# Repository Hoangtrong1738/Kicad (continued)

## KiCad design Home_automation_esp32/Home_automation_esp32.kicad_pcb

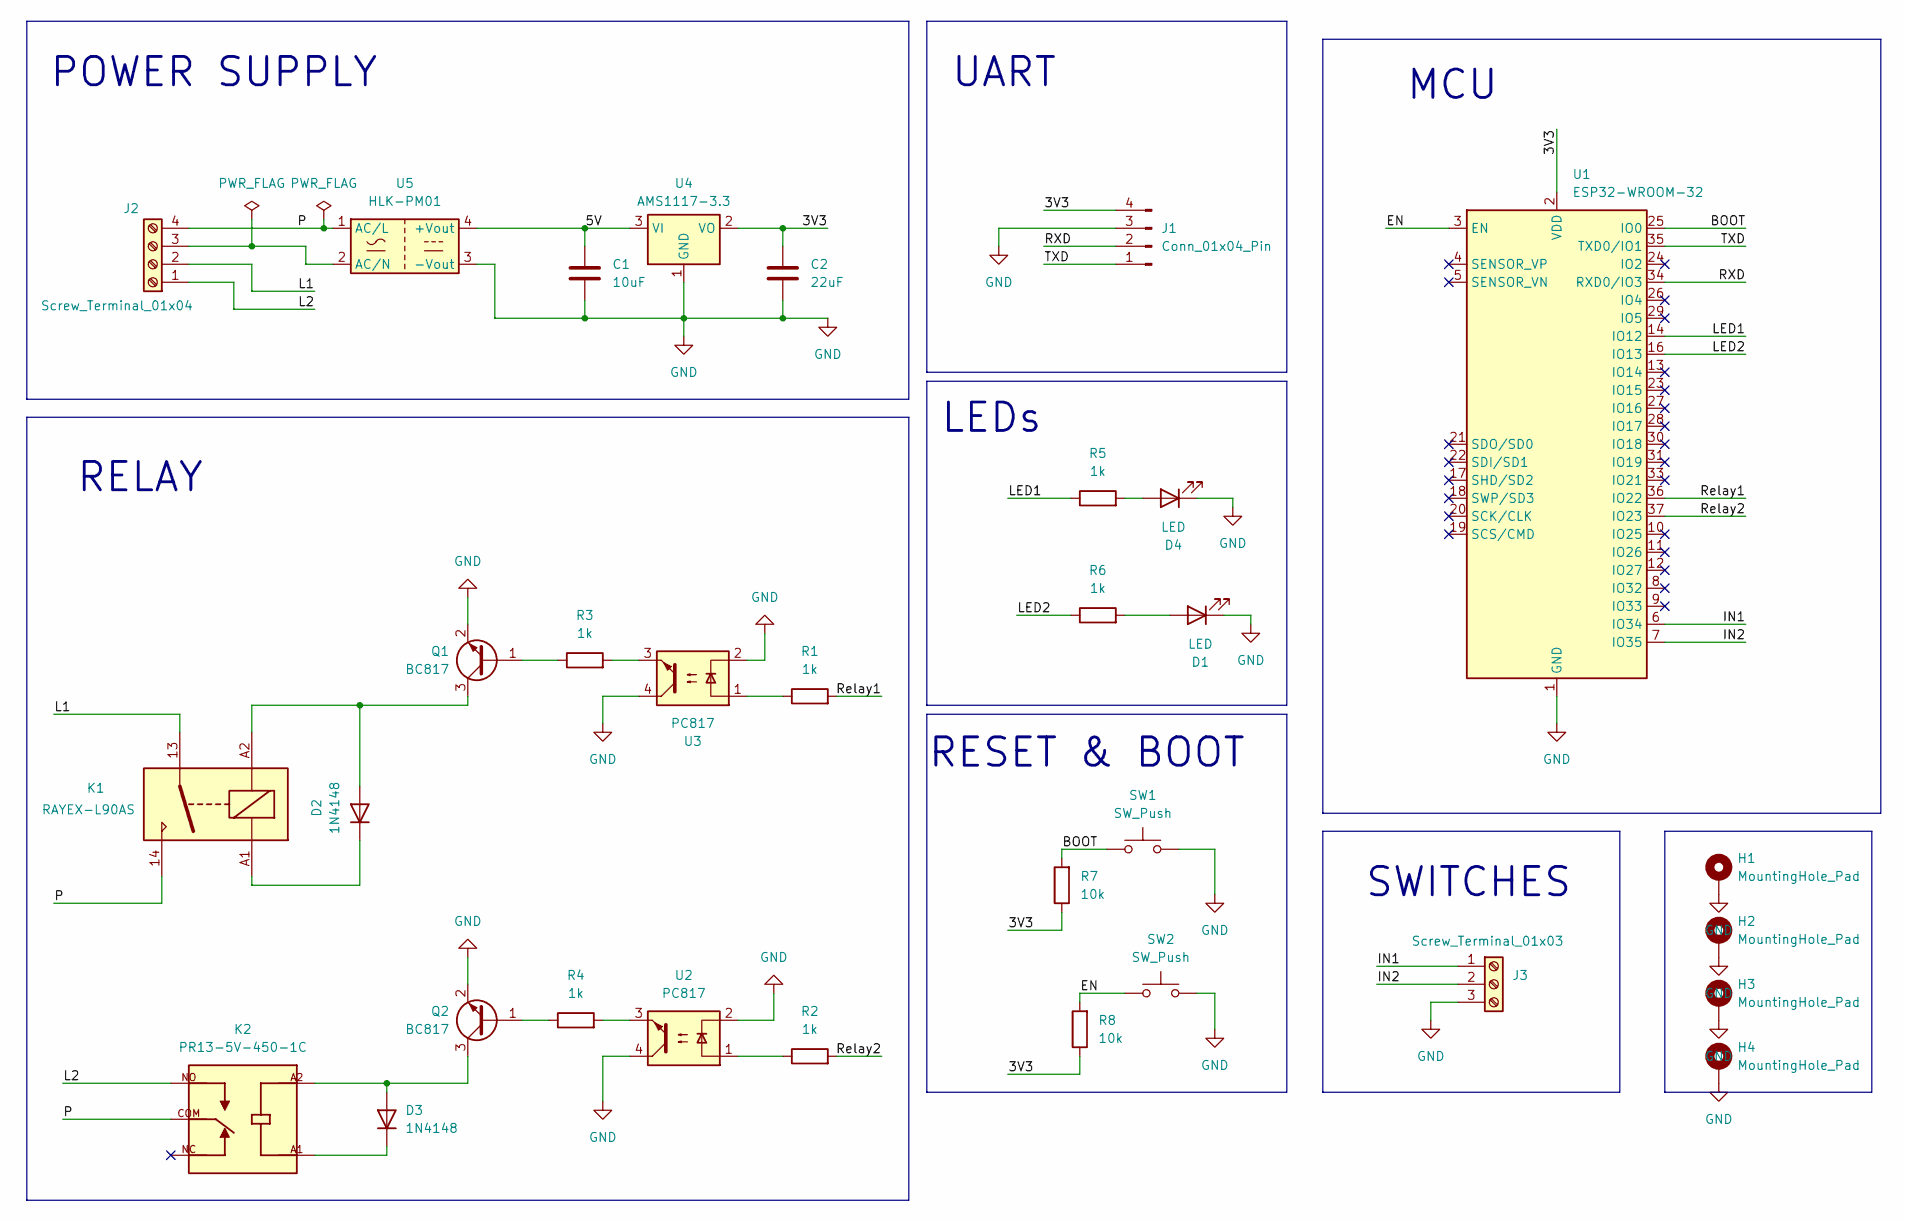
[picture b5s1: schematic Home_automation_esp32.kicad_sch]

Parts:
C1: 10uF; C_0805_2012Metric
C2: 22uF; C_0805_2012Metric
D1, D4: LED; LED_0805_2012Metric
D2, D3: 1N4148; D_DO-35_SOD27_P7.62mm_Horizontal
H1, H2, H3, H4: MountingHole_Pad; MountingHole_2.2mm_M2_DIN965_Pad
J1: Conn_01x04_Pin; PinHeader_1x04_P2.54mm_Vertical
J2: Screw_Terminal_01x04; TerminalBlock_MaiXu_MX126-5.0-04P_1x04_P5.00mm
J3: Screw_Terminal_01x03; TerminalBlock_MaiXu_MX126-5.0-03P_1x03_P5.00mm
K1: RAYEX-L90AS; Relay_SPST_RAYEX-L90AS
K2: PR13-5V-450-1C; RELAY_PR13-5V-450-1C; PARTREV 1.0
Q1, Q2: BC817; SOT-23
R1, R2, R3, R4, R5, R6: 1k; R_0805_2012Metric
R7, R8: 10k; R_0805_2012Metric
SW1, SW2: SW_Push; SW_PUSH_6mm
U1: ESP32-WROOM-32
U2, U3: PC817; DIP-4_W7.62mm
U4: AMS1117-3.3; SOT-223-3_TabPin2
U5: HLK-PM01; Converter_ACDC_Hi-Link_HLK-PMxx

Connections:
/3V3: C2.1, J1.4, R7.1, R8.1, U1.2 (VDD), U4.2 (VO)
/5V: C1.1, U4.3 (VI), U5.4 (+Vout)
/<NO NET>: R1.2, U1.36 (IO22)
/BOOT: R7.2, SW1.1, U1.25 (IO0)
/EN: R8.2, SW2.1, U1.3 (EN)
/IN1: J3.1, U1.6 (IO34)
/IN2: J3.2, U1.7 (IO35)
/L1: J2.2, K1.13
/L2: J2.1, K2.NO
/LED1: R5.1, U1.14 (IO12)
/LED2: R6.1, U1.16 (IO13)
/P: J2.4, K1.14, K2.COM, U5.1 (AC/L)
/RXD: J1.2, U1.34 (RXD0/IO3)
/Relay2: R2.2, U1.37 (IO23)
/TXD: J1.1, U1.35 (TXD0/IO1)
GND: C1.2, C2.2, D1.1 (K), D4.1 (K), H1.1 (1_1), H2.1 (1_1), H3.1 (1_1), H4.1 (1_1), J1.3, J3.3, Q1.2 (E), Q2.2 (E), SW1.2, SW2.2, U1.1 (GND), U1.15 (GND), U1.38 (GND), U1.39 (GND), U2.2, U2.4, U3.2, U3.4, U4.1 (GND), U5.3 (-Vout)
unnamed: D1.2 (A), R6.2
unnamed: D2.2 (A), K1.A2, Q1.3 (C)
unnamed: D2.1 (K), K1.A1
unnamed: D3.2 (A), K2.A2, Q2.3 (C)
unnamed: D3.1 (K), K2.A1
unnamed: D4.2 (A), R5.2
unnamed: J2.3, U5.2 (AC/N)
unnamed: Q1.1 (B), R3.1
unnamed: Q2.1 (B), R4.1
unnamed: R1.1, U3.1
unnamed: R2.1, U2.1
unnamed: R3.2, U3.3
unnamed: R4.2, U2.3

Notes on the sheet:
RESET & BOOT
MCU
UART
LEDs
RELAY
SWITCHES
POWER SUPPLY

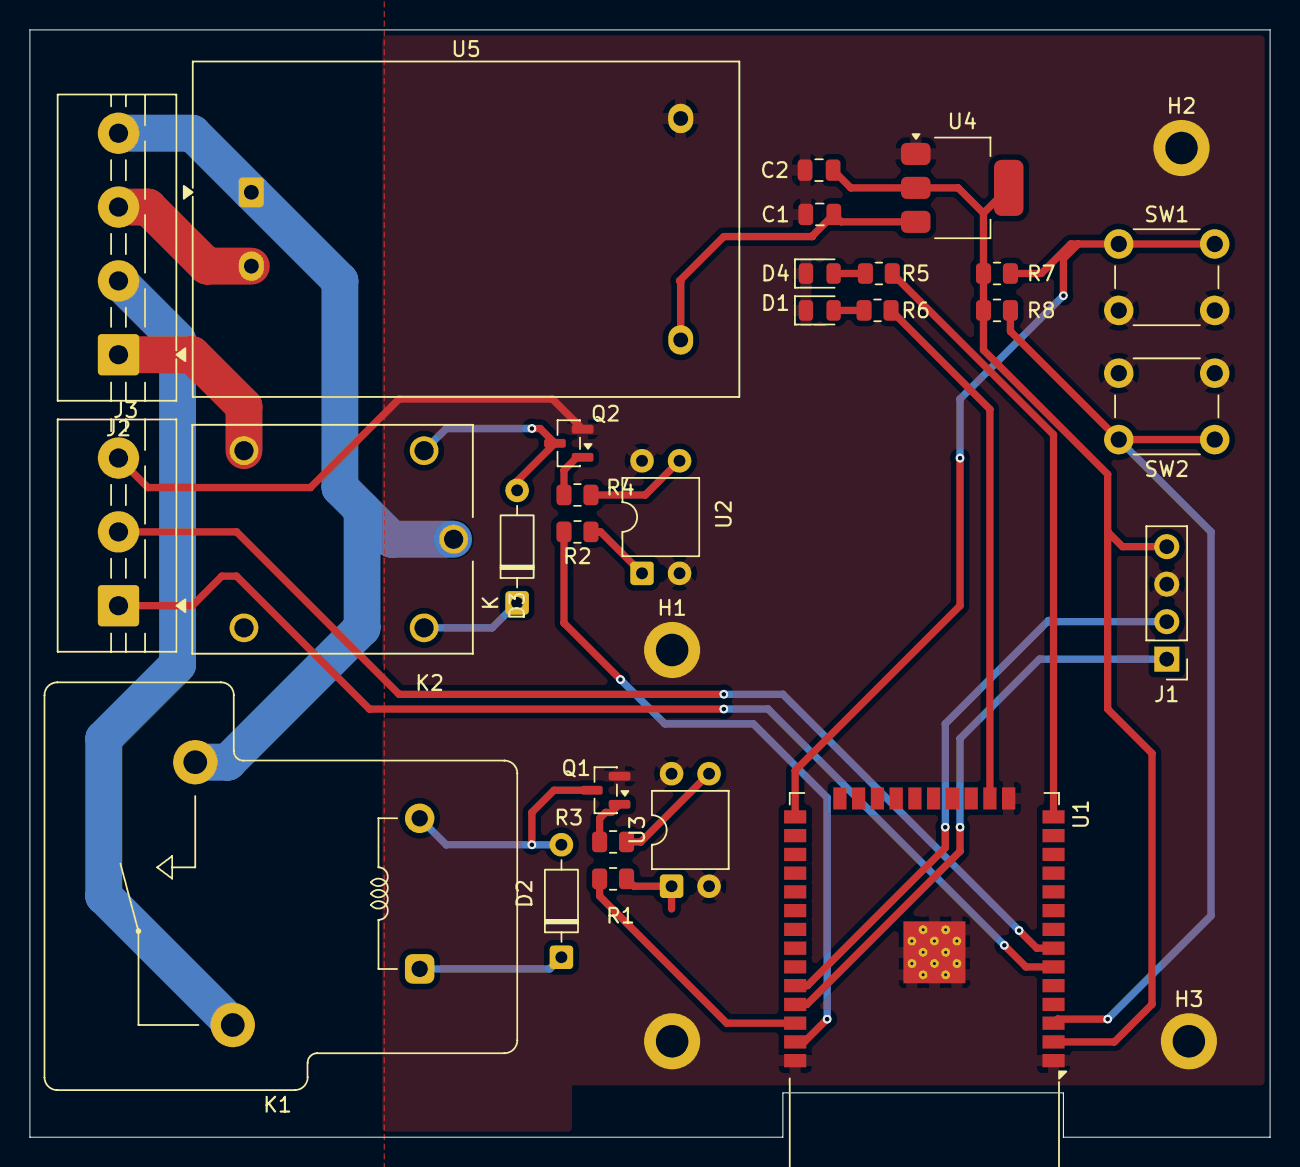
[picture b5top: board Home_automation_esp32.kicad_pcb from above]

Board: 2 copper layers, 84.0 x 75.0 mm, 32 parts (0 on the bottom side), 29 nets.

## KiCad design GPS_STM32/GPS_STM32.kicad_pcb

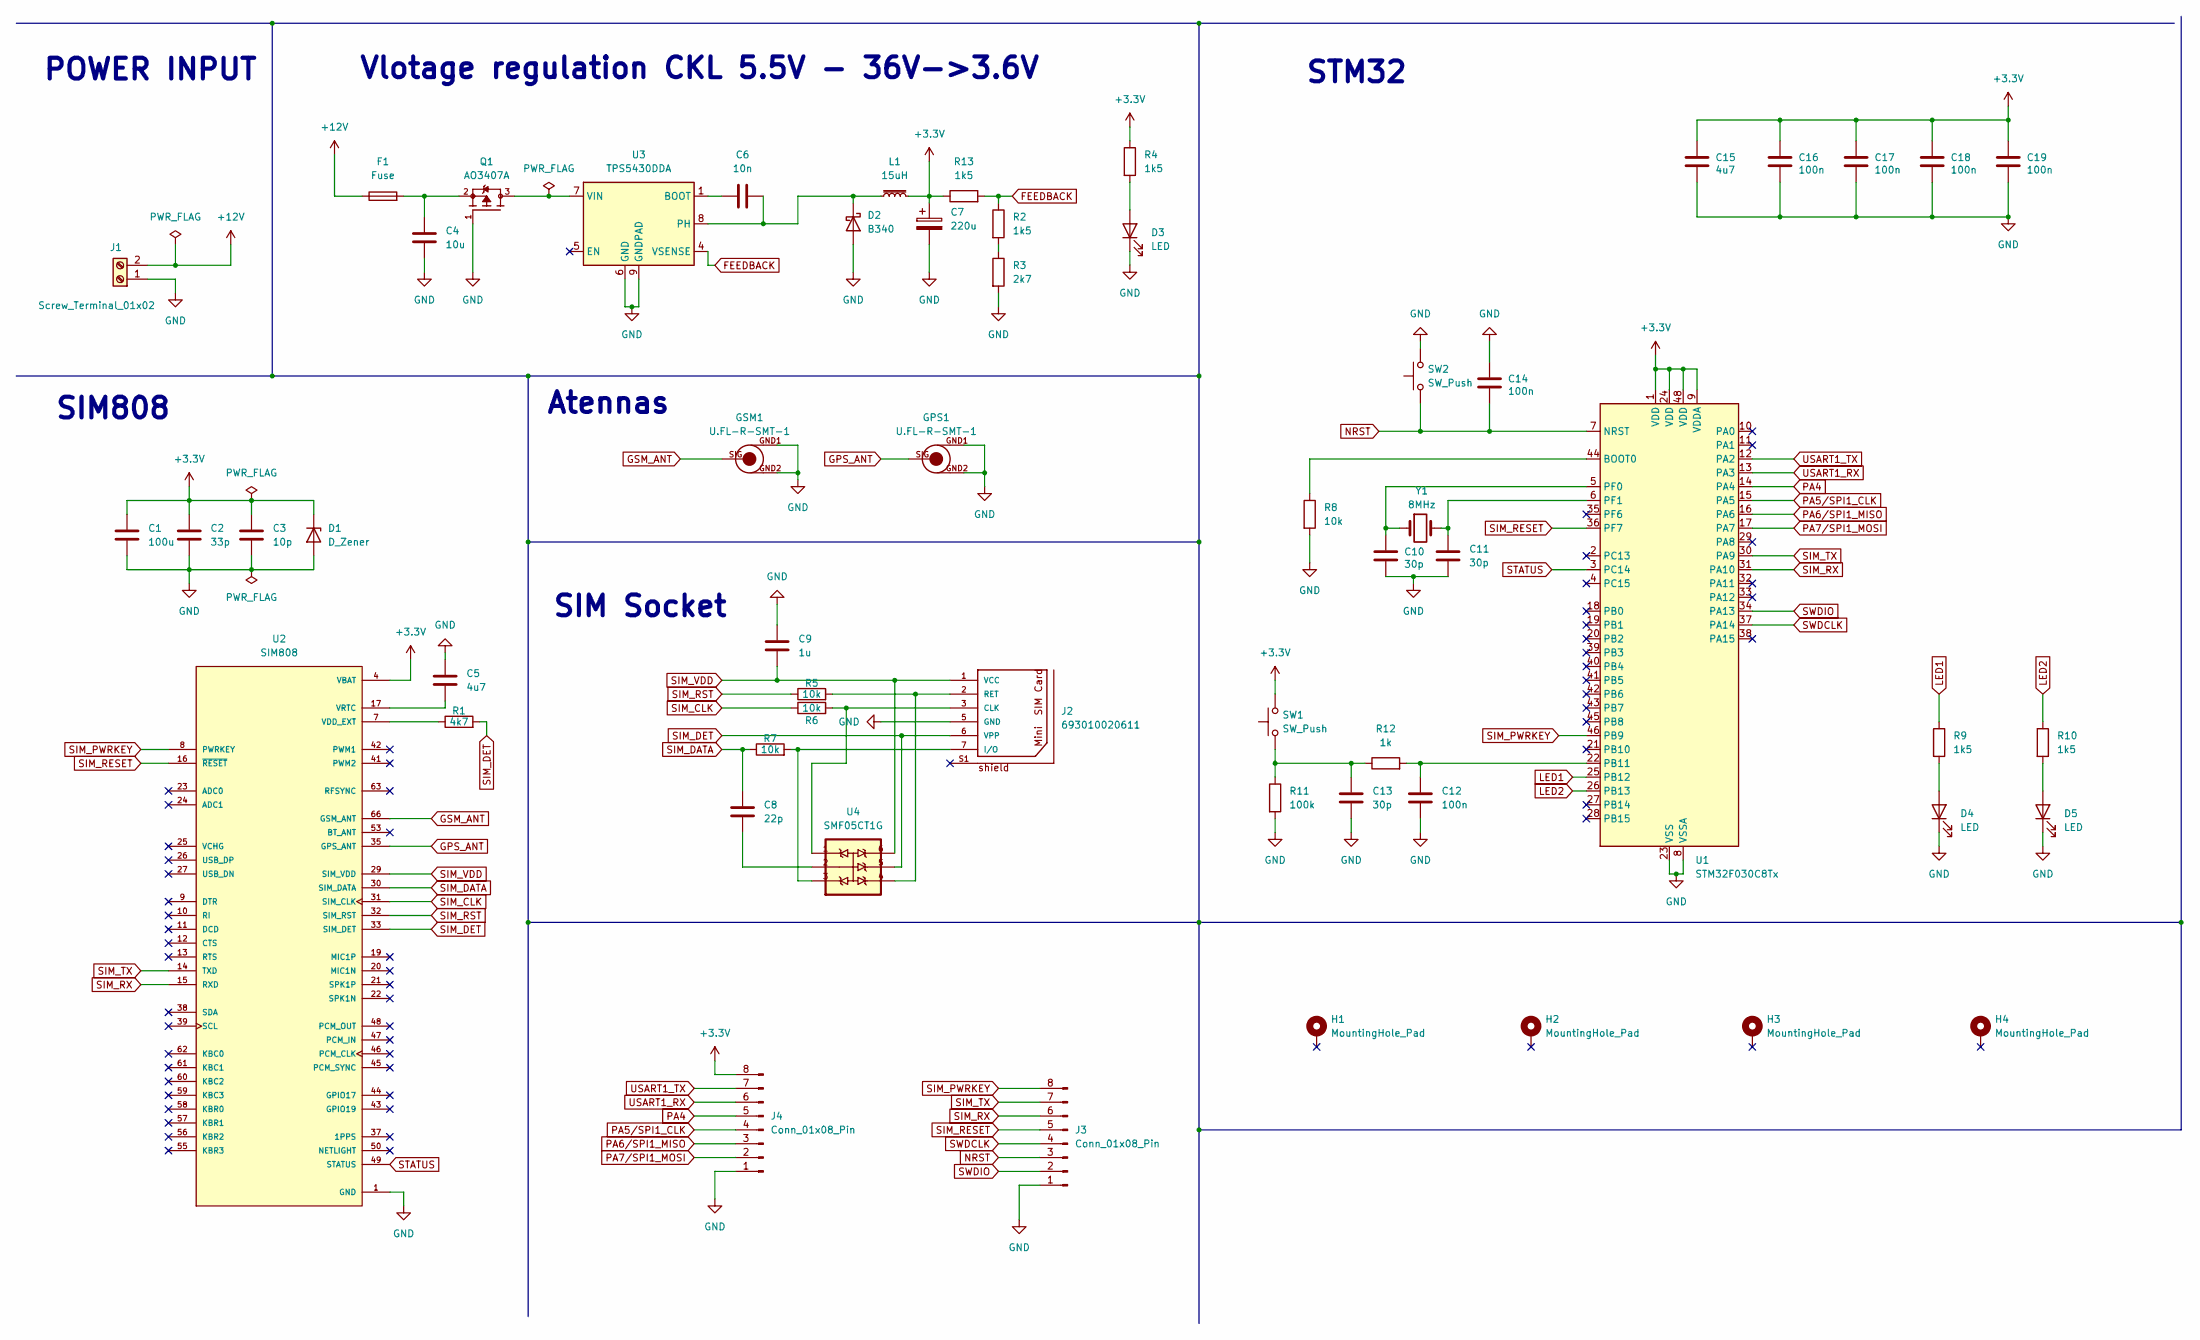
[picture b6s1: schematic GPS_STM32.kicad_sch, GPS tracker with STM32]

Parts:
C1: 100u; C_1206_3216Metric
C2: 33p; C_0402_1005Metric
C3: 10p; C_0402_1005Metric
C4: 10u; C_0805_2012Metric
C5, C15: 4u7; C_0201_0603Metric
C6: 10n; C_0201_0603Metric
C7: 220u; CP_EIA-7343-15_Kemet-W
C8: 22p; C_0402_1005Metric
C9: 1u; C_0402_1005Metric
C10, C11, C13: 30p; C_0402_1005Metric
C12, C14, C19: 100n; C_0402_1005Metric
C16, C17, C18: 100n; C_0402_1005Metric_Pad0.74x0.62mm_HandSolder
D1: D_Zener; D_0805_2012Metric
D2: B340; D_SMC
D3, D4, D5: LED; LED_0201_0603Metric
F1: Fuse; LED_0201_0603Metric
GPS1: U.FL-R-SMT-1
GSM1: U.FL-R-SMT-1
H1, H2, H3, H4: MountingHole_Pad; MountingHole_2.2mm_M2_Pad_Via
J1: Screw_Terminal_01x02; TerminalBlock_Phoenix_MKDS-1,5-2-5.08_1x02_P5.08mm_Horizont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
J2: 693010020611
J3, J4: Conn_01x08_Pin; PinHeader_1x08_P2.54mm_Vertical
L1: 15uH; L_10.4x10.4_H4.8
Q1: AO3407A; SOT95P280X125-3N; PARTREV 5
R1: 4k7; R_0402_1005Metric
R2, R4, R9, R10, R13: 1k5; R_0805_2012Metric
R3: 2k7; R_0805_2012Metric
R5, R6, R7, R8: 10k; R_0402_1005Metric
R11: 100k; R_0201_0603Metric
R12: 1k; R_0603_1608Metric
SW1, SW2: SW_Push; SW_Push_1P1T_NO_CK_KSC6xxJ
U1: STM32F030C8Tx; LQFP-48_7x7mm_P0.5mm
U2: SIM808; XCVR_SIM808; PARTREV 1.03
U3: TPS5430DDA; TI_SO-PowerPAD-8_ThermalVias
U4: SMF05CT1G; SOT65P210X110-6N
Y1: 8MHz; Crystal_SMD_5032-2Pin_5.0x3.2mm

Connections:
+3.3V: C1.1, C2.1, C3.1, C7.1, C15.1, C16.1, C17.1, C18.1, C19.1, D1.1 (K), J4.8, L1.2, R4.1, R13.1, SW1.2, U1.1 (VDD), U1.9 (VDDA), U1.24 (VDD), U1.48 (VDD), U2.4 (VBAT), U2.5 (VBAT), U2.6 (VBAT)
+12V: F1.1, J1.2
FEEDBACK: R2.1, R13.2, U3.4 (VSENSE)
GND: C1.2, C2.2, C3.2, C4.2, C5.1, C7.2, C9.1, C10.2, C11.2, C12.2, C13.2, C14.1, C15.2, C16.2, C17.2, C18.2, C19.2, D1.2 (A), D2.2 (A), D3.1 (K), D4.1 (K), D5.1 (K), GPS1.GND1, GPS1.GND2, GSM1.GND1, GSM1.GND2, J1.1, J2.5 (GND), J3.1, J4.1, Q1.1, R3.2, R8.2, R11.2, SW2.2, U1.8 (VSSA), U1.23 (VSS), U1.47 (VSS), U2.1 (GND), U2.2 (GND), U2.3 (GND), U2.18 (GND), U2.28 (GND), U2.34 (GND), U2.36 (GND), U2.40 (GND), U2.51 (GND), U2.52 (GND), U2.54 (GND), U2.64 (GND), U2.65 (GND), U2.67 (GND), U2.68 (GND), U3.6 (GND), U3.9 (GNDPAD)
GPS_ANT: GPS1.SIG, U2.35 (GPS_ANT)
GSM_ANT: GSM1.SIG, U2.66 (GSM_ANT)
LED1: R9.1, U1.25 (PB12)
LED2: R10.1, U1.26 (PB13)
NRST: C14.2, J3.3, SW2.1, U1.7 (NRST)
unnamed: C4.1, F1.2, Q1.2
unnamed: C8.2, U4.2
unnamed: C13.1, R11.1, R12.1, SW1.1
unnamed: C6.2, D2.1 (K), L1.1, U3.8 (PH)
unnamed: D3.2 (A), R4.2
unnamed: D4.2 (A), R9.2
unnamed: D5.2 (A), R10.2
unnamed: J2.3 (CLK), R6.2, U4.1
unnamed: J2.7 (I/O), R7.2, U4.3
unnamed: J2.2 (RET), R5.2, U4.4
unnamed: R2.2, R3.1
unnamed: R8.1, U1.44 (BOOT0)
unnamed: C12.1, R12.2, U1.22 (PB11)
unnamed: C10.1, U1.5 (PF0), Y1.1
unnamed: C11.1, U1.6 (PF1), Y1.2
unnamed: R1.1, U2.7 (VDD_EXT)
unnamed: C5.2, U2.17 (VRTC)
unnamed: C6.1, U3.1 (BOOT)
unnamed: Q1.3, U3.7 (VIN)
PA4: J4.5, U1.14 (PA4)
PA5/SPI1_CLK: J4.4, U1.15 (PA5)
PA6/SPI1_MISO: J4.3, U1.16 (PA6)
PA7/SPI1_MOSI: J4.2, U1.17 (PA7)
SIM_CLK: R6.1, U2.31 (SIM_CLK)
SIM_DATA: C8.1, R7.1, U2.30 (SIM_DATA)
SIM_DET: J2.6 (VPP), R1.2, U2.33 (SIM_DET), U4.5
SIM_PWRKEY: J3.8, U1.46 (PB9), U2.8 (PWRKEY)
SIM_RESET: J3.5, U1.36 (PF7), U2.16 (~RESET)
SIM_RST: R5.1, U2.32 (SIM_RST)
SIM_RX: J3.6, U1.31 (PA10), U2.15 (RXD)
SIM_TX: J3.7, U1.30 (PA9), U2.14 (TXD)
SIM_VDD: C9.2, J2.1 (VCC), U2.29 (SIM_VDD), U4.6
STATUS: U1.3 (PC14), U2.49 (STATUS)
SWDCLK: J3.4, U1.37 (PA14)
SWDIO: J3.2, U1.34 (PA13)
USART1_RX: J4.6, U1.13 (PA3)
USART1_TX: J4.7, U1.12 (PA2)

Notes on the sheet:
SIM808
Vlotage regulation CKL 5.5V - 36V->3.6V
STM32
POWER INPUT
SIM Socket
Atennas

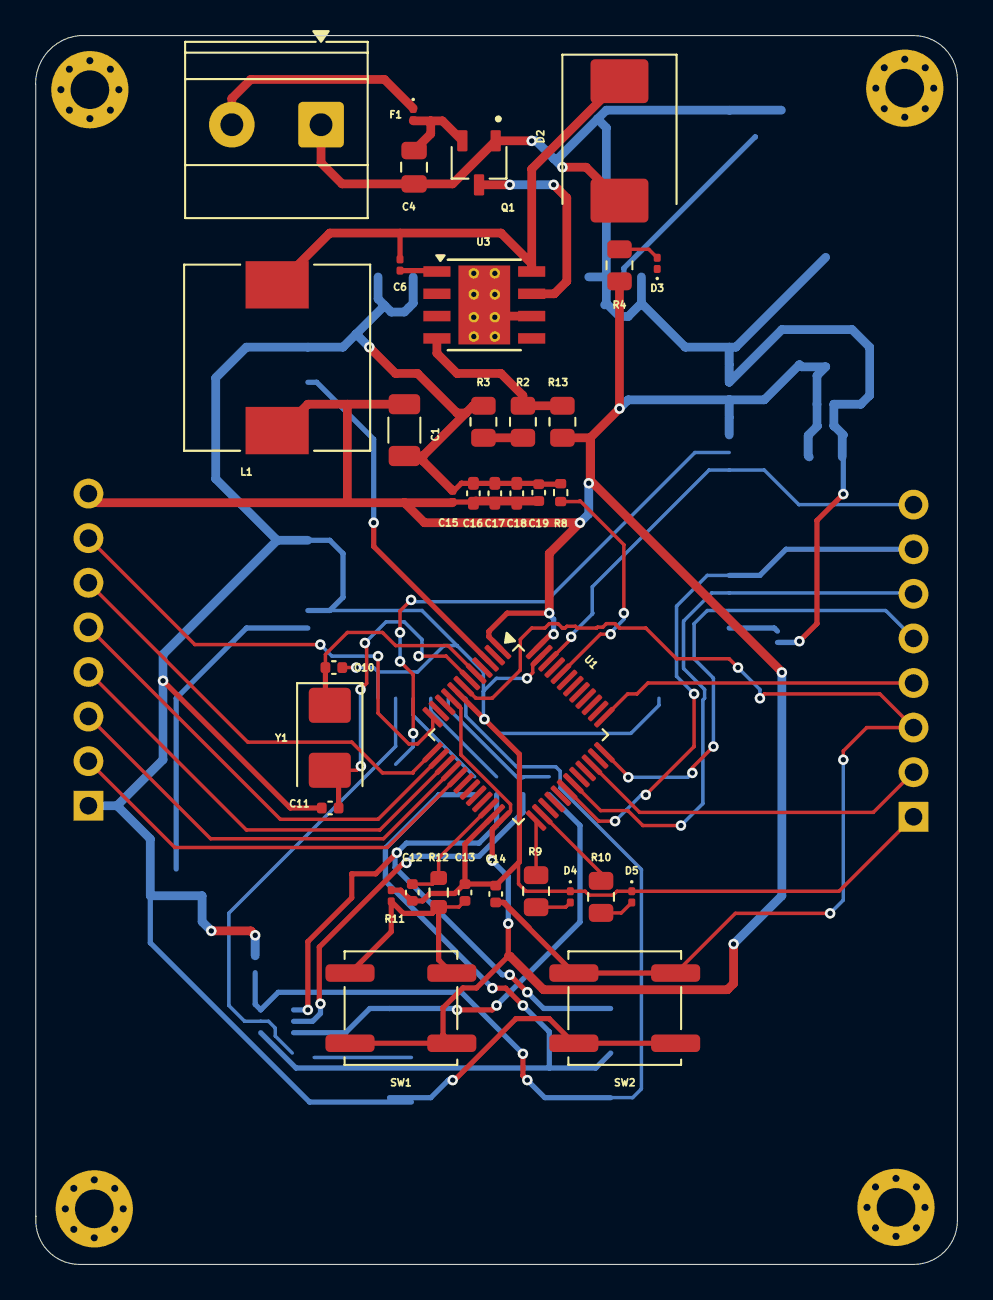
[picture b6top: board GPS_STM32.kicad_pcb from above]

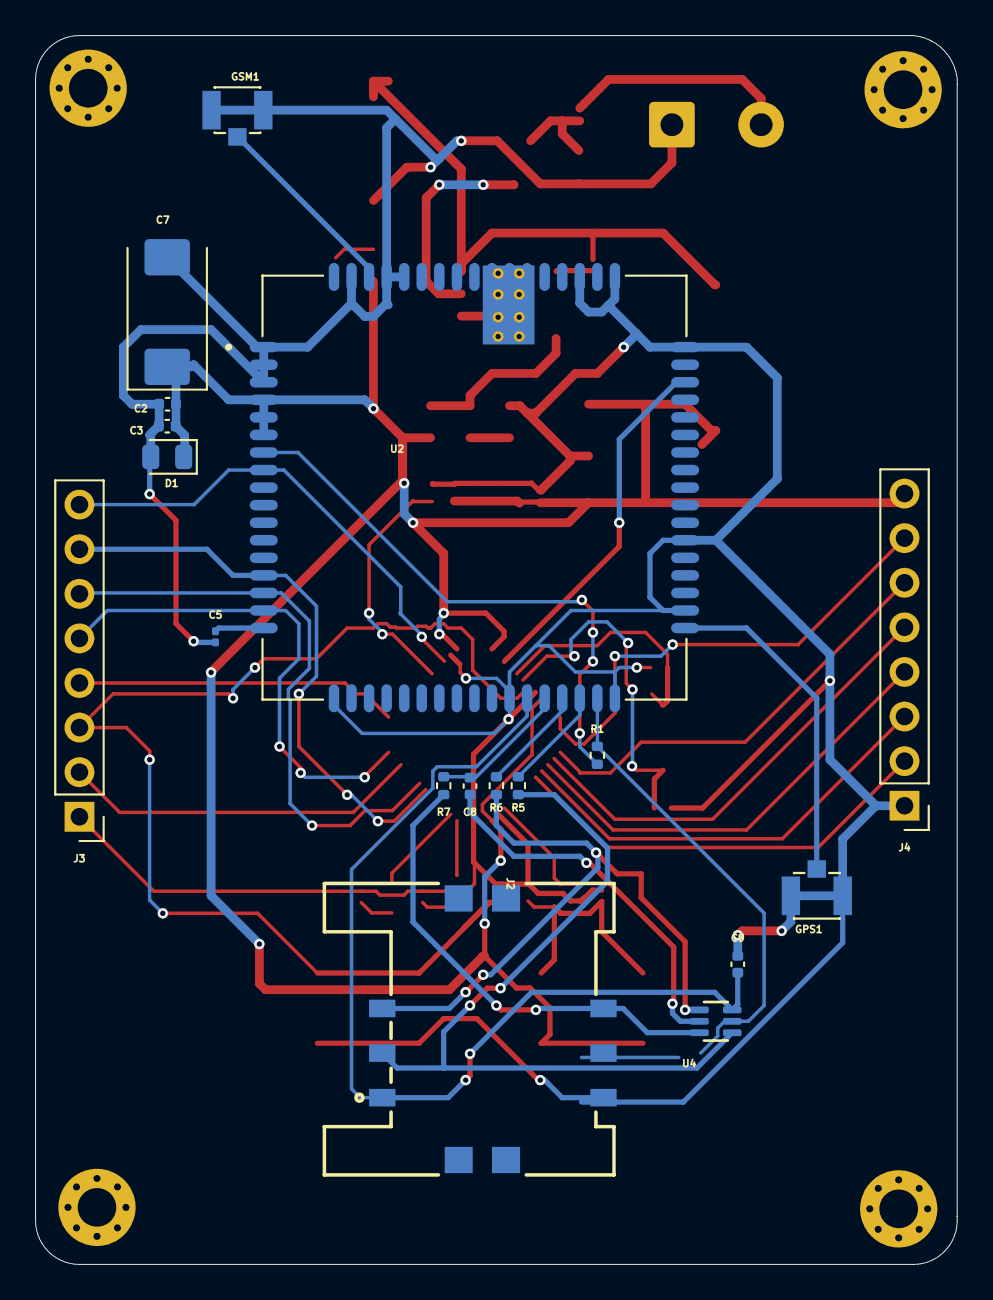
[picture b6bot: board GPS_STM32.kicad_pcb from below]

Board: 4 copper layers, 52.5 x 70.0 mm, 57 parts (18 on the bottom side), 46 nets.

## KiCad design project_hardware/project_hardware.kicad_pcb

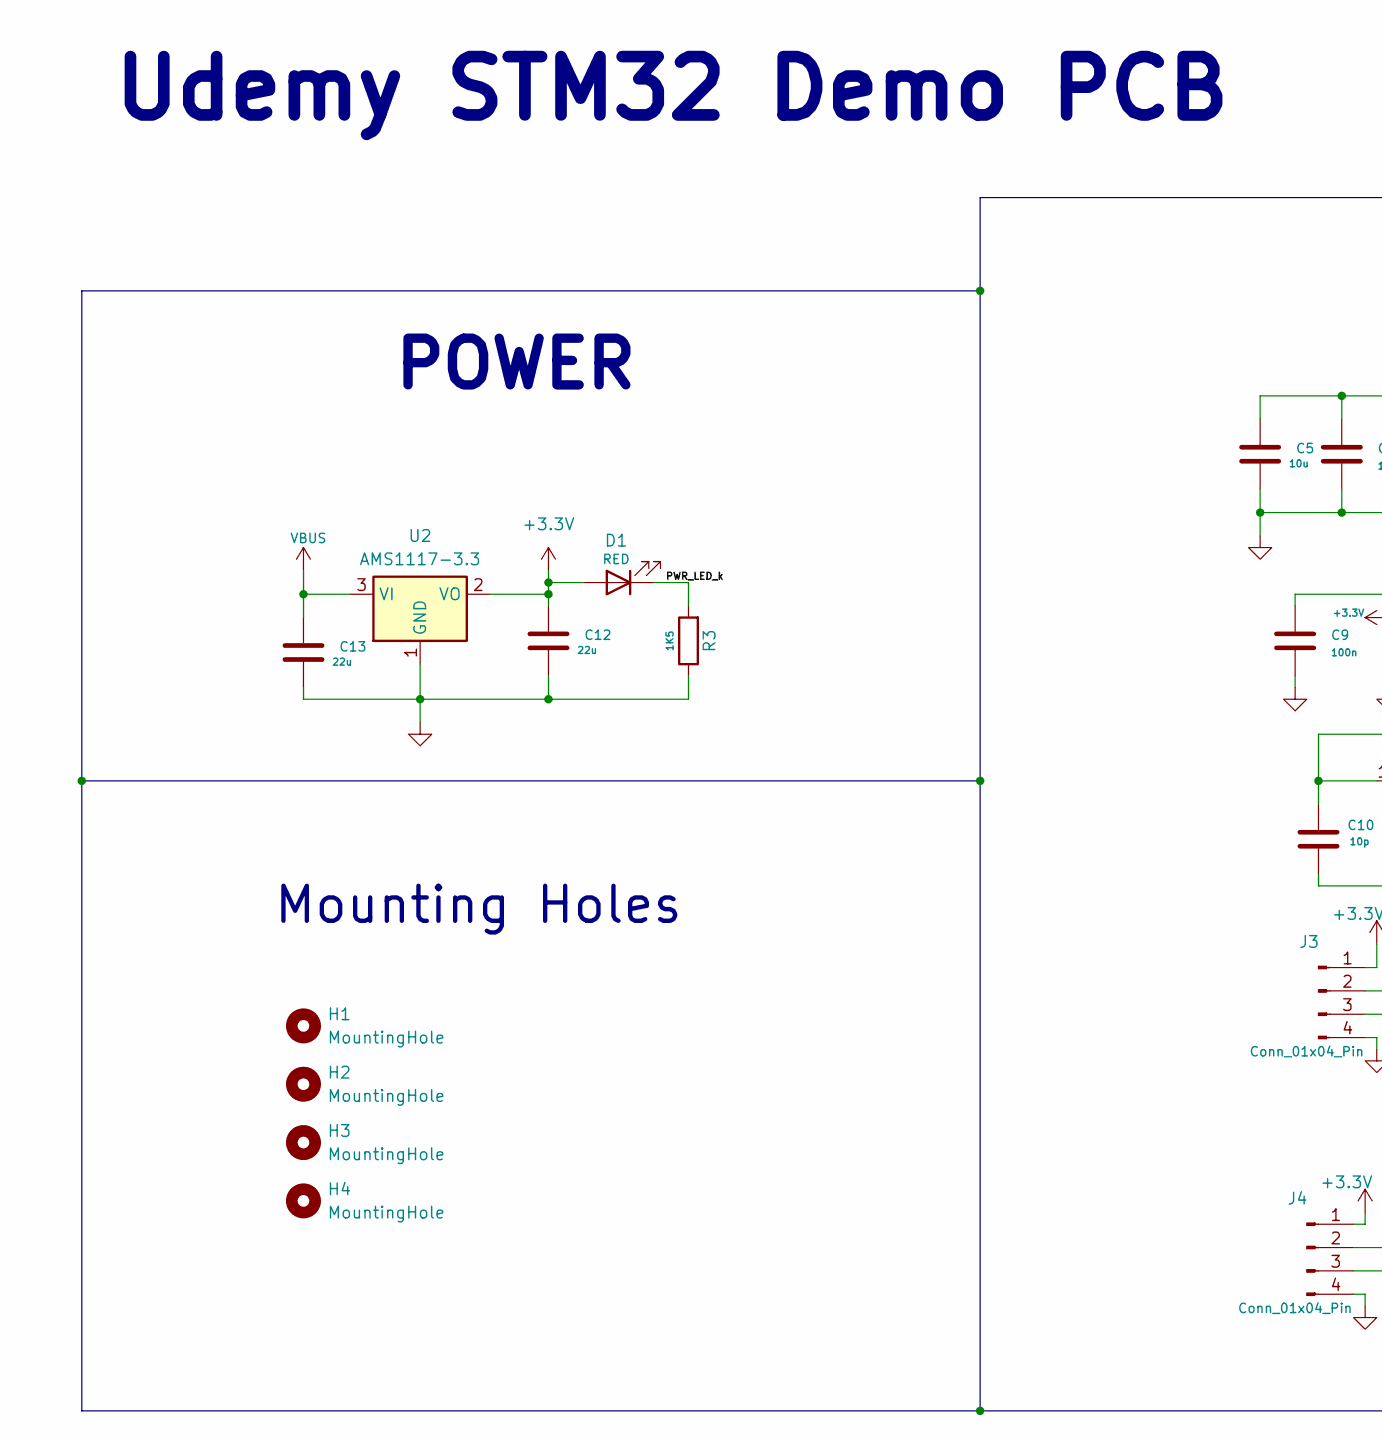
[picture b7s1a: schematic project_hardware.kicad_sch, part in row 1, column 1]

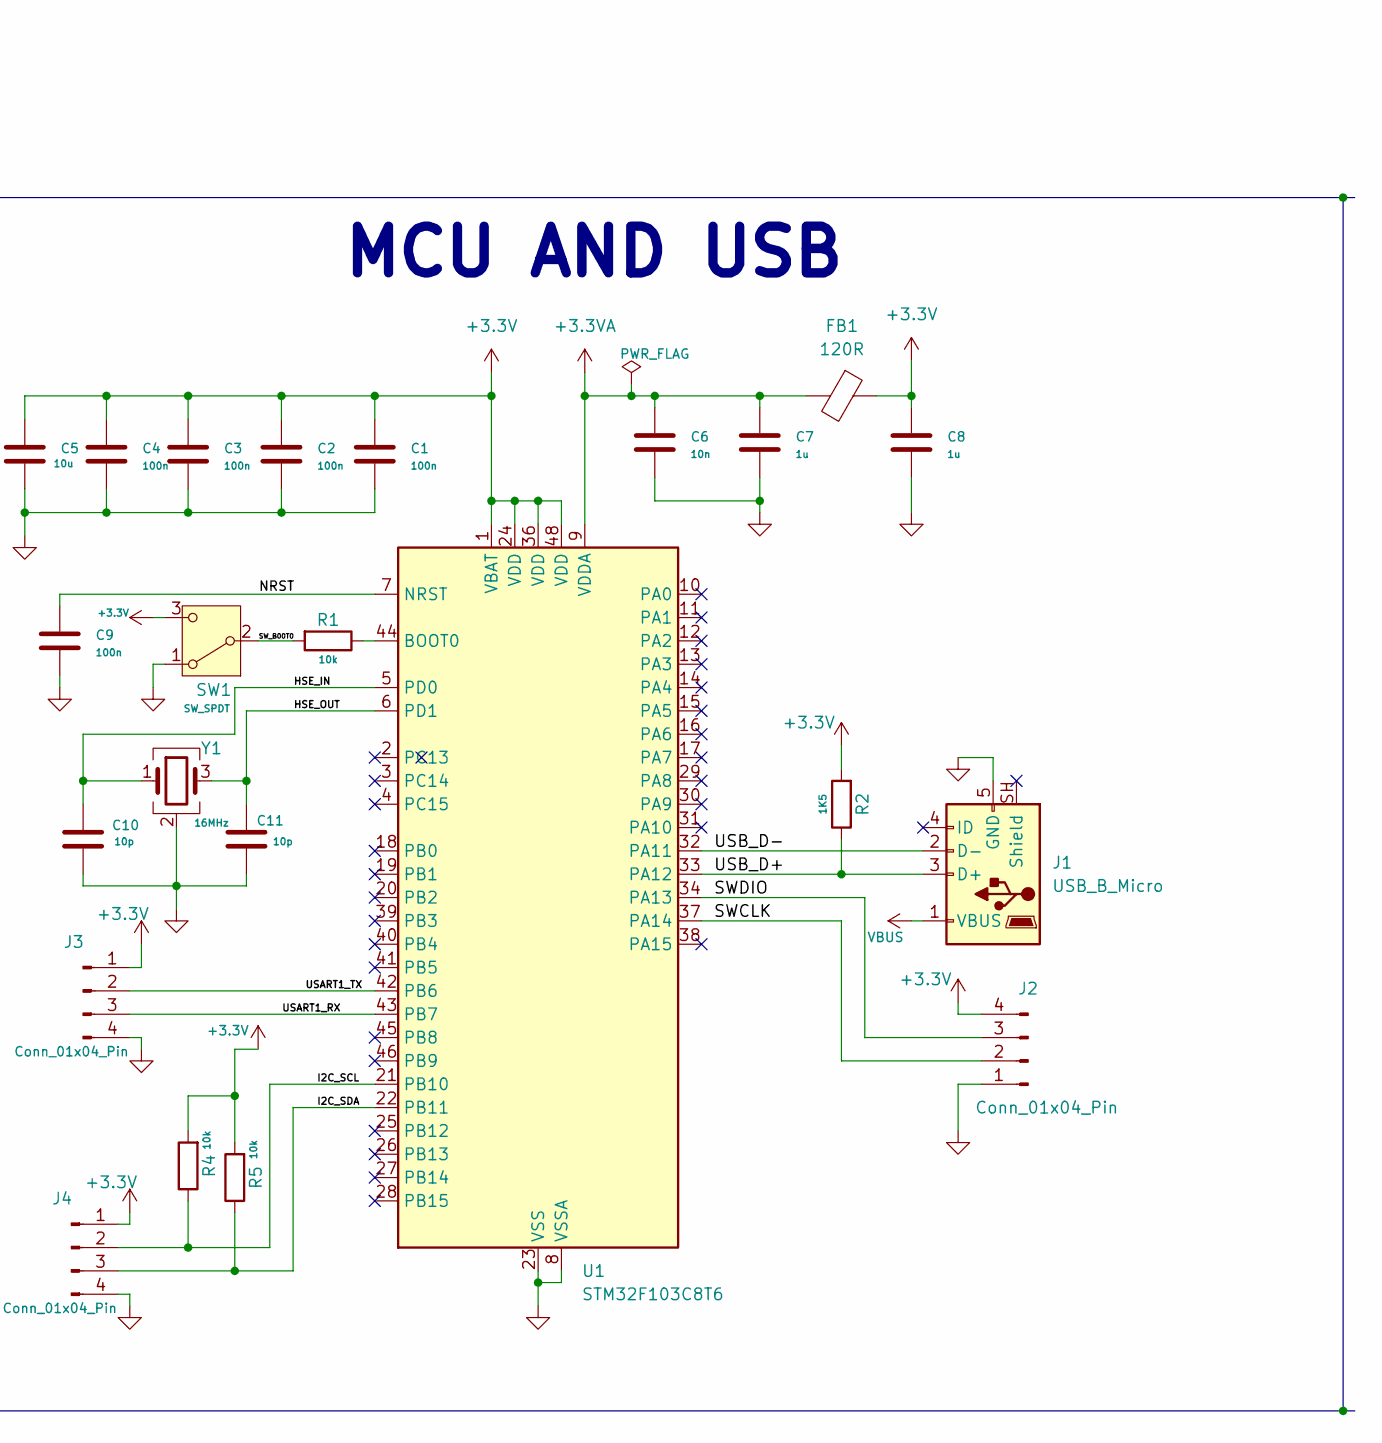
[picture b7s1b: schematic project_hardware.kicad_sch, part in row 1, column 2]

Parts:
C1, C2, C3, C4, C9: 100n; C_0402_1005Metric
C5: 10u; C_0603_1608Metric
C6: 10n; C_0402_1005Metric
C7, C8: 1u; C_0402_1005Metric
C10, C11: 10p; C_0402_1005Metric
C12, C13: 22u; C_0805_2012Metric
D1: RED; LED_0603_1608Metric
FB1: 120R; L_0603_1608Metric
H1, H2, H3, H4: MountingHole; MountingHole_2.2mm_M2
J1: USB_B_Micro; USB_Micro-B_Wuerth_629105150521
J2, J3, J4: Conn_01x04_Pin; PinHeader_1x04_P2.54mm_Vertical
R1, R4, R5: 10k; R_0402_1005Metric
R2, R3: 1K5; R_0402_1005Metric
SW1: SW_SPDT; SW_SPDT_PCM12
U1: STM32F103C8T6; LQFP-48_7x7mm_P0.5mm
U2: AMS1117-3.3; SOT-223-3_TabPin2
Y1: 16MHz; Crystal_SMD_3225-4Pin_3.2x2.5mm

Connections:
+3.3V: C1.1, C2.1, C3.1, C4.1, C5.1, C8.1, C12.1, D1.2 (A), FB1.1, J2.4, J3.1, J4.1, R2.2, R4.2, R5.2, SW1.3 (C), U1.1 (VBAT), U1.24 (VDD), U1.36 (VDD), U1.48 (VDD), U2.2 (VO)
+3.3VA: C6.1, C7.1, FB1.2, U1.9 (VDDA)
/<NO NET>: J3.3, U1.43 (PB7)
/HSE_IN: C10.1, U1.5 (PD0), Y1.1
/HSE_OUT: C11.1, U1.6 (PD1), Y1.3
/I2C_SCL: J4.2, R4.1, U1.21 (PB10)
/I2C_SDA: J4.3, R5.1, U1.22 (PB11)
/NRST: C9.1, U1.7 (NRST)
/PWR_LED_k: D1.1 (K), R3.2
/SWCLK: J2.2, U1.37 (PA14)
/SWDIO: J2.3, U1.34 (PA13)
/SW_B00T0: R1.2, SW1.2 (B)
/USART1_TX: J3.2, U1.42 (PB6)
/USB_D+: J1.3 (D+), R2.1, U1.33 (PA12)
/USB_D-: J1.2 (D-), U1.32 (PA11)
GND: C1.2, C2.2, C3.2, C4.2, C5.2, C6.2, C7.2, C8.2, C9.2, C10.2, C11.2, C12.2, C13.2, J1.5 (GND), J2.1, J3.4, J4.4, R3.1, SW1.1 (A), U1.8 (VSSA), U1.23 (VSS), U1.35 (VSS), U1.47 (VSS), U2.1 (GND), Y1.2 (G), Y1.4 (G)
unnamed: R1.1, U1.44 (BOOT0)
VBUS: C13.1, J1.1 (VBUS), U2.3 (VI)

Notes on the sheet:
Udemy STM32 Demo PCB
POWER
Mounting Holes
MCU AND USB

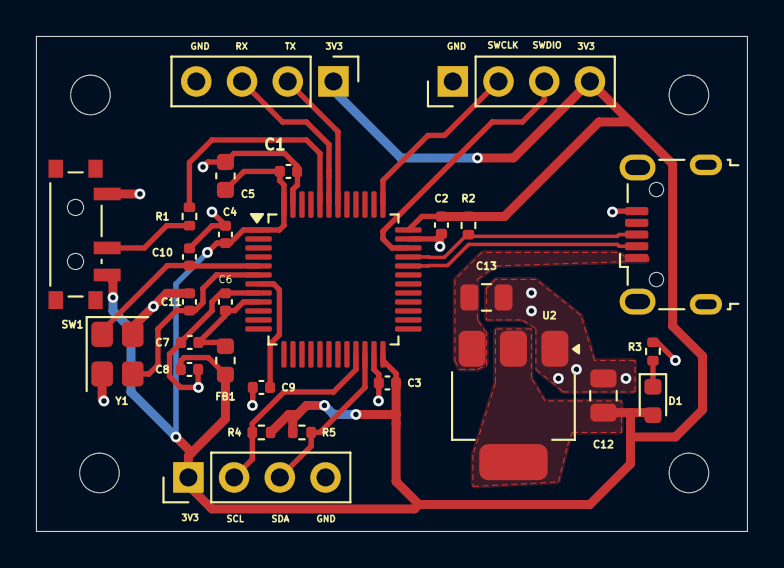
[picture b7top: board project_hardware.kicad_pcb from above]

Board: 2 copper layers, 39.5 x 27.5 mm, 32 parts (0 on the bottom side), 18 nets.

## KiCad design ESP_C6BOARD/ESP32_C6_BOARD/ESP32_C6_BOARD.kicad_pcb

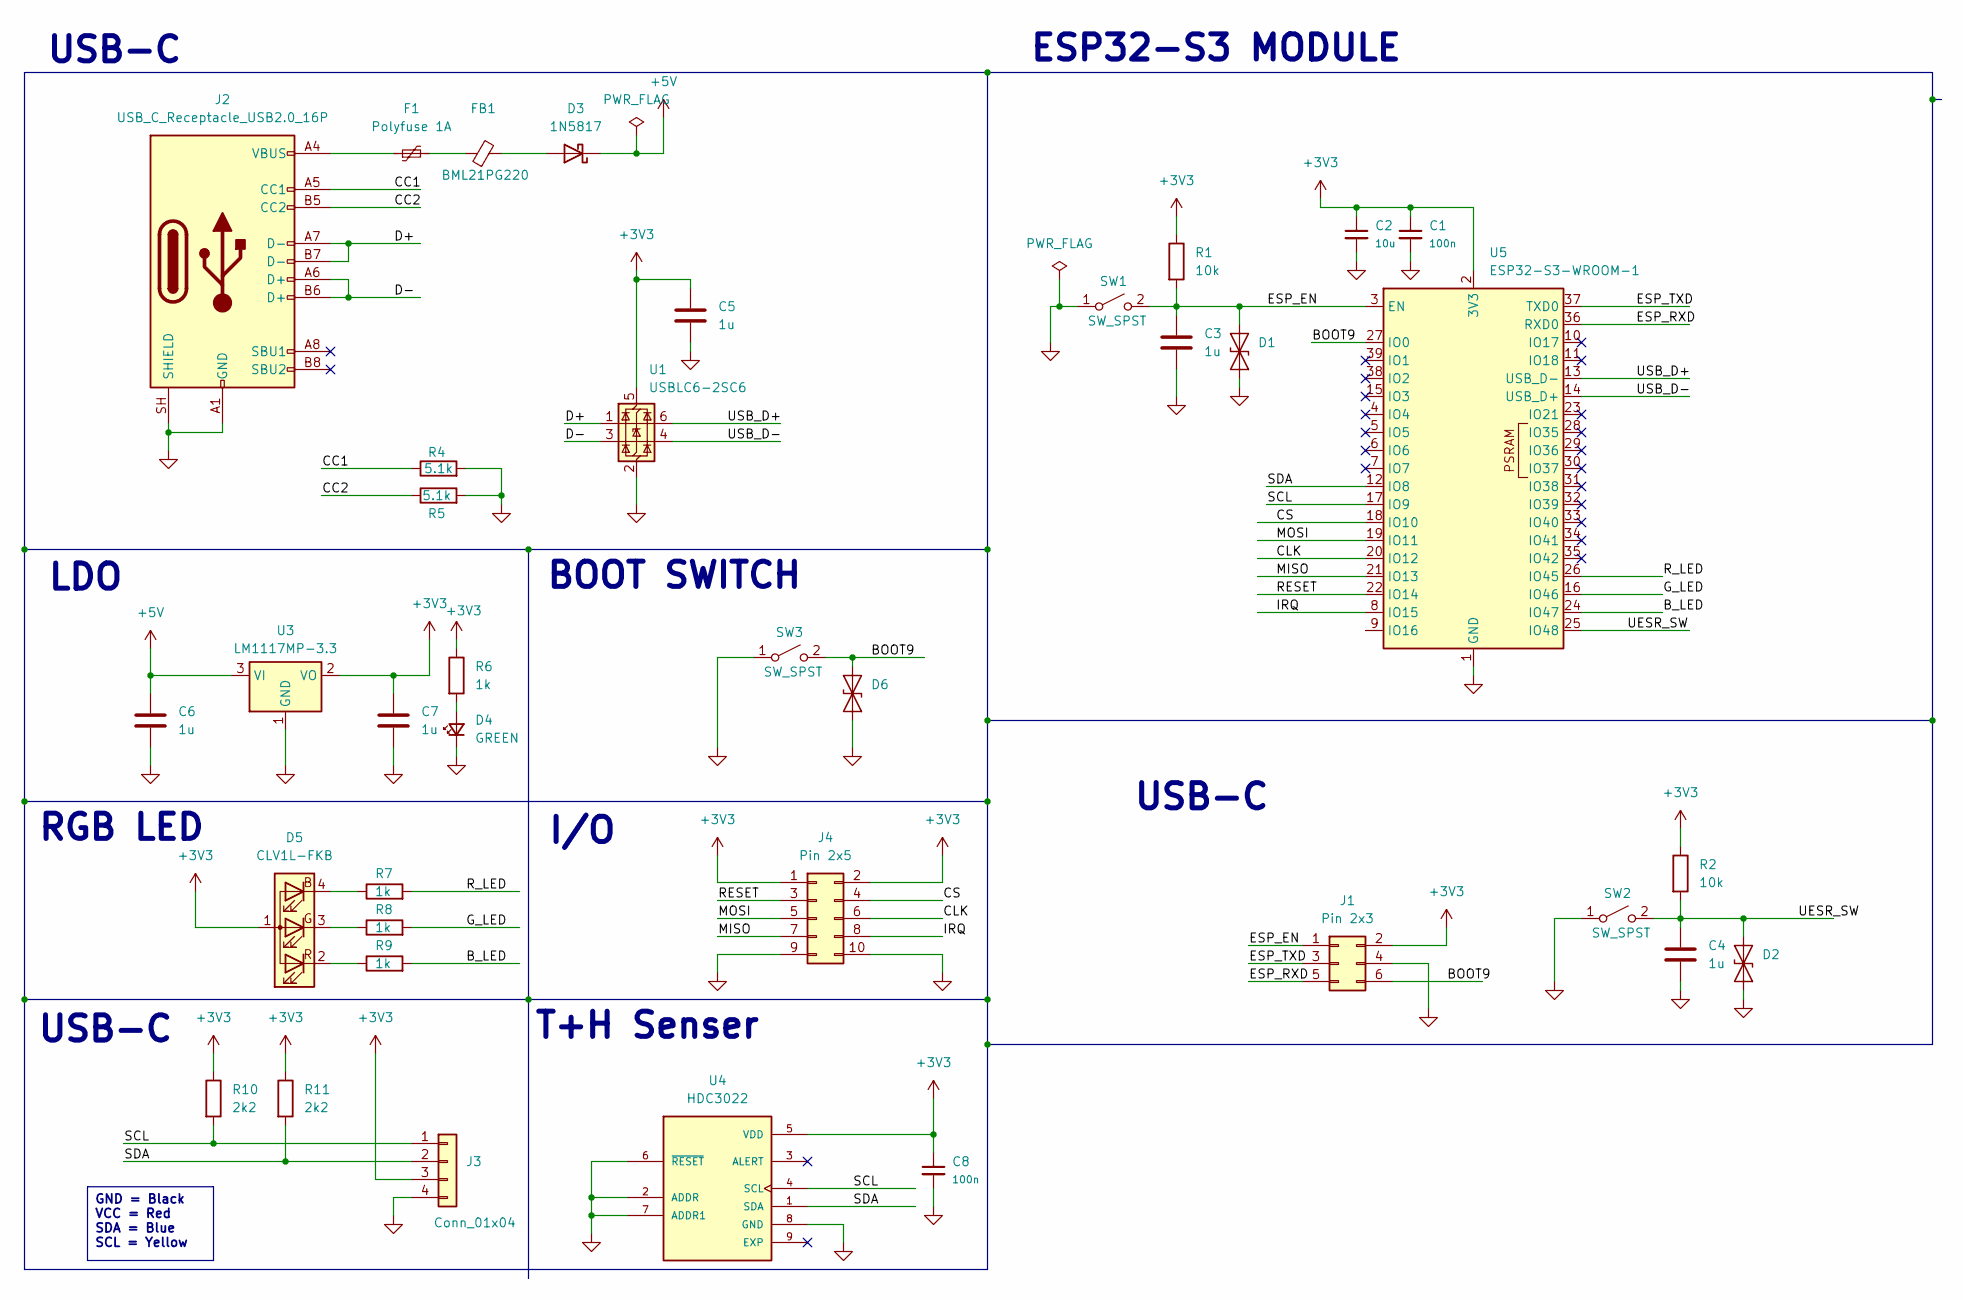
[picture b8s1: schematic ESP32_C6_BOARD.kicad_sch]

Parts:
C1, C8: 100n; C_0603_1608Metric
C2: 10u; C_0805_2012Metric
C3, C4, C5, C6, C7: 1u; C_0603_1608Metric
D1, D2, D6: D_SOD-923
D3: 1N5817; D_DO-41_SOD81_P10.16mm_Horizontal
D4: GREEN; LED_0603_1608Metric
D5: CLV1L-FKB; LED_Cree-PLCC4_3.2x2.8mm_CCW
F1: Polyfuse 1A; Fuse_0805_2012Metric
FB1: BML21PG220; L_0805_2012Metric
J1: Pin 2x3; PinHeader_2x03_P2.54mm_Vertical
J2: USB_C_Receptacle_USB2.0_16P; USB_C_Receptacle_GCT_USB4105-xx-A_16P_TopMnt_Horizontal
J3: Conn_01x04; PinHeader_1x04_P2.54mm_Vertical
J4: Pin 2x5; PinHeader_2x05_P2.54mm_Vertical
R1, R2: 10k; R_0603_1608Metric
R4, R5: 5.1k; R_0603_1608Metric
R6, R7, R8, R9: 1k; R_0603_1608Metric
R10, R11: 2k2; R_0603_1608Metric
SW1, SW2, SW3: SW_SPST; SW_SPST_PTS810
U1: USBLC6-2SC6; SOT-23-6
U3: LM1117MP-3.3; SOT-223-3_TabPin2
U4: HDC3022; XDCR_HDC3022QDEJRQ1; PARTREV D
U5: ESP32-S3-WROOM-1; ESP32-S3-WROOM-1U

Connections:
+3V3: C1.1, C2.1, C5.1, C7.1, C8.1, D5.1 (A), J1.2, J3.3, J4.1, J4.2, R1.1, R2.1, R6.1, R10.1, R11.1, U1.5 (VBUS), U3.2 (VO), U4.5 (VDD), U5.2 (3V3); also elsewhere on the board
+5V: C6.1, D3.1 (K), U3.3 (VI)
/BOOT9: D6.2 (A2), J1.6, SW3.2 (B), U5.27 (IO0)
/B_LED: R9.2, U5.24 (IO47)
/CC1: J2.A5 (CC1), R4.1
/CC2: J2.B5 (CC2), R5.1
/CLK: J4.6, U5.20 (IO12)
/CS: J4.4, U5.18 (IO10)
/D+: J2.A7 (D-), J2.B7 (D-), U1.1 (I/O1)
/D-: J2.A6 (D+), J2.B6 (D+), U1.3 (I/O2)
/ESP_EN: C3.1, D1.2 (A2), J1.1, R1.2, SW1.2 (B), U5.3 (EN)
/ESP_RXD: J1.5, U5.36 (RXD0)
/ESP_TXD: J1.3, U5.37 (TXD0)
/G_LED: R8.2, U5.16 (IO46)
/IRQ: J4.8, U5.8 (IO15)
/MISO: J4.7, U5.21 (IO13)
/MOSI: J4.5, U5.19 (IO11)
/RESET: J4.3, U5.22 (IO14)
/R_LED: R7.2, U5.26 (IO45)
/SCL: J3.1, R10.2, U4.4 (SCL), U5.17 (IO9)
/SDA: J3.2, R11.2, U4.1 (SDA), U5.12 (IO8)
/UESR_SW: C4.1, D2.2 (A2), R2.2, SW2.2 (B), U5.25 (IO48)
/USB_D+: U1.6 (I/O1), U5.13 (USB_D-)
/USB_D-: U1.4 (I/O2), U5.14 (USB_D+)
GND: C1.2, C2.2, C3.2, C4.2, C5.2, C6.2, C7.2, C8.2, D1.1 (A1), D2.1 (A1), D4.1 (K), D6.1 (A1), J1.4, J2.A1 (GND), J2.A12 (GND), J2.B1 (GND), J2.B12 (GND), J2.SH (SHIELD), J3.4, J4.9, J4.10, R4.2, R5.2, SW1.1 (A), SW2.1 (A), SW3.1 (A), U1.2 (GND), U3.1 (GND), U4.2 (ADDR), U4.6 (~RESET), U4.7 (ADDR1), U4.8 (GND), U5.1 (GND), U5.40 (GND), U5.41 (GND)
unnamed: D3.2 (A), FB1.2
unnamed: D4.2 (A), R6.2
unnamed: D5.4 (BK), R7.1
unnamed: D5.3 (GK), R8.1
unnamed: D5.2 (RK), R9.1
unnamed: F1.1, J2.A4 (VBUS), J2.A9 (VBUS), J2.B4 (VBUS), J2.B9 (VBUS)
unnamed: F1.2, FB1.1

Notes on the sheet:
ESP32-S3 MODULE
LDO
BOOT SWITCH
RGB LED
T+H Senser
USB-C
I/O
GND = Black VCC = Red SDA = Blue SCL = Yellow

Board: 2 copper layers, 37 parts (0 on the bottom side), 32 nets, no tracks yet.

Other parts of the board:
R3: 10k; R_0603_1608Metric

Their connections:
+3V3: R3.1; also elsewhere on the board
